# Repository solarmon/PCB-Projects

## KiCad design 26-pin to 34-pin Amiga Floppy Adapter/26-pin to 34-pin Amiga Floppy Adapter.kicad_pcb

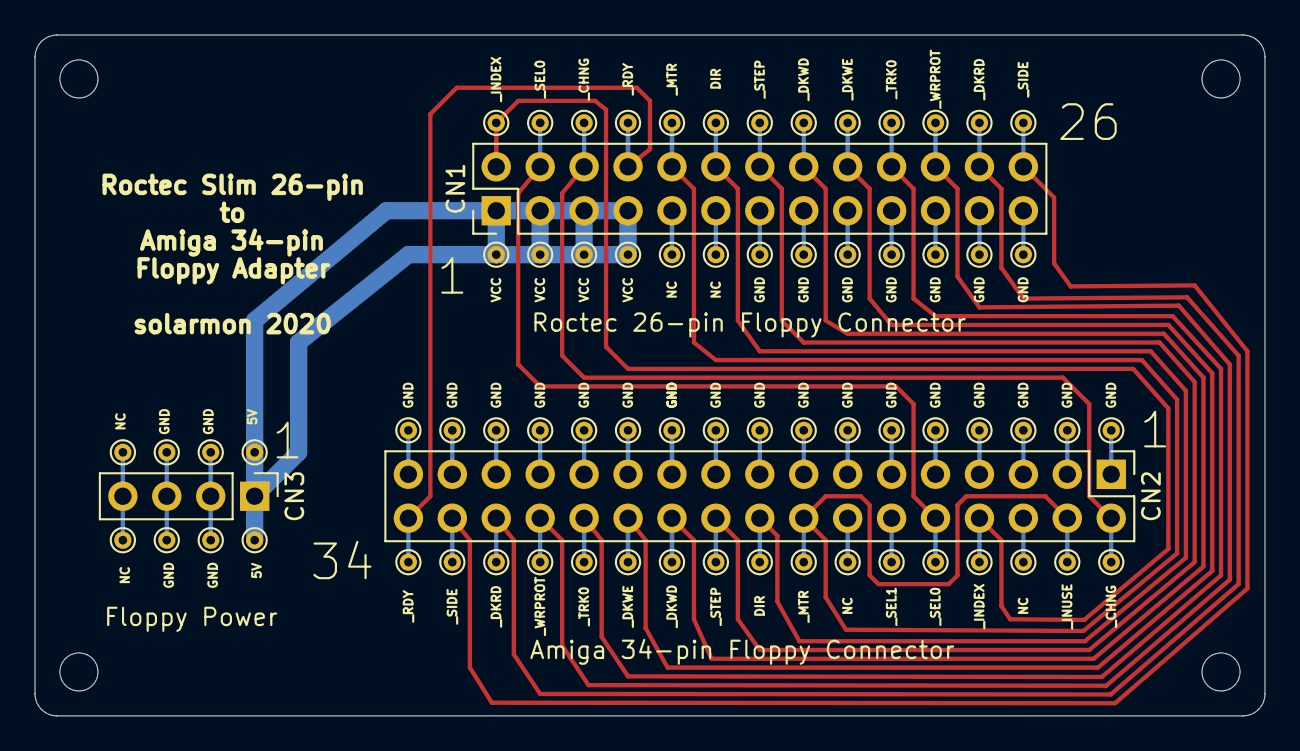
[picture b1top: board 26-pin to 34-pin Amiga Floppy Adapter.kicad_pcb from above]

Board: 2 copper layers, 71.1 x 39.4 mm, 3 parts (0 on the bottom side), 15 nets.

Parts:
CN1: Conn_02x13_Odd_Even; PinHeader_2x13_P2.54mm_Vertical
CN2: Conn_02x17_Odd_Even; PinHeader_2x17_P2.54mm_Vertical
CN3: Conn_01x04; PinHeader_1x04_P2.54mm_Vertical

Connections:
/DIR: CN1.12, CN2.18
/_CHNG: CN1.6, CN2.2
/_DKRD: CN1.24, CN2.30
/_DKWD: CN1.16, CN2.22
/_DKWE: CN1.18, CN2.24
/_INDEX: CN1.2, CN2.8
/_INUSE: CN1.10, CN2.4, CN2.16
/_RDY: CN1.8, CN2.34
/_SEL0: CN1.4, CN2.10
/_SIDE: CN1.26, CN2.32
/_STEP: CN1.14, CN2.20
/_TRK0: CN1.20, CN2.26
/_WRPROT: CN1.22, CN2.28
GND: CN1.13, CN1.15, CN1.17, CN1.19, CN1.21, CN1.23, CN1.25, CN2.1, CN2.3, CN2.5, CN2.7, CN2.9, CN2.11, CN2.13, CN2.15, CN2.17, CN2.19, CN2.21, CN2.23, CN2.25, CN2.27, CN2.29, CN2.31, CN2.33, CN3.2, CN3.3
VCC: CN1.1, CN1.3, CN1.5, CN1.7, CN3.1

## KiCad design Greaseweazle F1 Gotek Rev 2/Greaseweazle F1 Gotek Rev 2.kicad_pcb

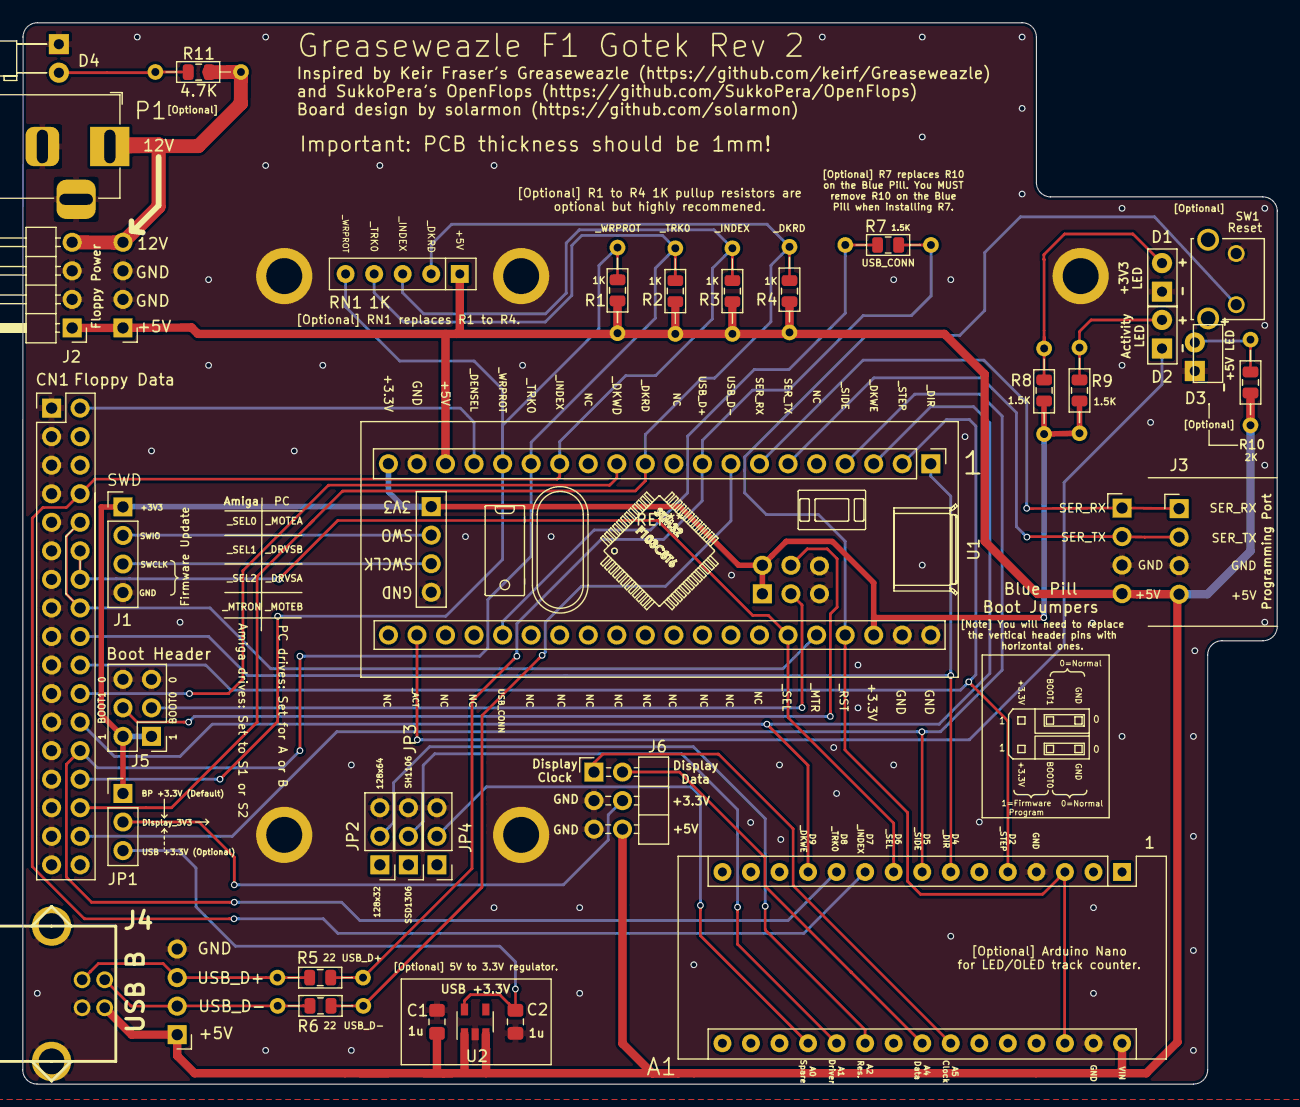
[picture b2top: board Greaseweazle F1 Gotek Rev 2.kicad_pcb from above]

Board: 2 copper layers, 111.6 x 94.4 mm, 53 parts (0 on the bottom side), 40 nets.

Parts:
A1: Arduino_Nano_v3.x; Arduino_Nano
C1, C2: 1u; C_0805_2012Metric_Pad1.15x1.40mm_HandSolder
CN1: Floppy Data; PinHeader_2x17_P2.54mm_Vertical
D1: +3V3 LED; LED_D3.0mm_Horizontal_O6.35mm_Z10.0mm
D2: ACT LED; LED_D3.0mm_Horizontal_O6.35mm_Z10.0mm
D3, D4: +5V LED; LED_D3.0mm_Horizontal_O3.81mm_Z6.0mm
H1, H2, H3, H4, H5: MountingHole_Pad; MountingHole_M3_Pad
J1: SWD; PinHeader_1x04_P2.54mm_Vertical
J1#2, J2, J3: PinHeader_1x04_P2.54mm_Vertical; PinHeader_1x04_P2.54mm_Horizontal
J2#2: Floppy Power; PinHeader_1x04_P2.54mm_Horizontal
J3#2: Programming Port; PinHeader_1x04_P2.54mm_Horizontal
J4: USB B; conn_usb_B
J5: Boot Header; PinHeader_2x03_P2.54mm_Vertical
J6: LEDC68; PinHeader_2x03_P2.54mm_Horizontal
JP1: +3.3V Jumper; PinHeader_1x03_P2.54mm_Vertical
JP2: OLED Resolution; PinHeader_1x03_P2.54mm_Vertical
JP3: OLED Driver; PinHeader_1x03_P2.54mm_Vertical
JP4: SPARE; PinHeader_1x03_P2.54mm_Vertical
P1: 12V Power; BarrelJack_Horizontal
R1, R2, R3, R4, R5, R6, R7, R8, R9, R10, R11: R_Axial_DIN0204_L3.6mm_D1.6mm_P7.62mm_Horizontal
R1#2, R2#2, R3#2, R4#2: 1K; R_0805_2012Metric
R5#2, R6#2: 22; R_0805_2012Metric
R7#2, R8#2, R9#2: 1.5K; R_0805_2012Metric
R10#2: 2K; R_0805_2012Metric
R11#2: 4.7K; R_0805_2012Metric
RN1: 1K; R_Array_SIP5
SW1: Reset; PUSH_BUTTON_RIGHT_ANGLE
U1: Blue Pill; YAAJ_BluePill_SWD_1_BootPins
U2: AP2112K-3.3; SOT-23-5

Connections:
+3V3: J1.1, J5.1, J5.2, JP1.1, R8.2, R8#2.2, R9.2, R9#2.2, U1.20, U1.38, U1.41, U1.45, U1.48
+5V: A1.30, C1.1, J1#2.1, J2.1, J2#2.1, J3.4, J3#2.4, J4.1, J6.6, R1.1, R1#2.1, R2.1, R2#2.1, R3.1, R3#2.1, R4.1, R4#2.1, R10.2, R10#2.2, RN1.1, U1.18, U2.1, U2.3
+12V: J2.4, J2#2.4, P1.1, R11.1, R11#2.2
/BOOT0: J5.3, U1.46
/BOOT1: J5.4, U1.49
/Display_3V3: J6.4, JP1.2
/Display_Clock: A1.24, J6.1
/Display_Data: A1.23, J6.2
/JP_OLED_DR: A1.20, JP3.2
/JP_OLED_RES: A1.21, JP2.2
/JP_SPARE: A1.19, JP4.2
/SER_RX: J3.1, J3#2.1, U1.7
/SER_TX: J3.2, J3#2.2, U1.6
/SWD_SWCLK: J1.3, U1.43
/SWD_SWIO: J1.2, U1.42
/USB_3V3: C2.1, JP1.3, U2.5
/USB_CONN: R7.2, R7#2.2, U1.25
/USB_D+: R5.2, R5#2.2, R7.1, R7#2.1, U1.9
/USB_D-: R6.2, R6#2.2, U1.8
/_ACT: D2.1, U1.22
/_DENSEL: CN1.2, U1.17
/_DIR: A1.7, CN1.18, U1.1
/_DKRD: CN1.30, R4.2, R4#2.2, RN1.2, U1.11
/_DKWD: CN1.22, U1.12
/_DKWE: A1.12, CN1.24, U1.3
/_INDEX: A1.10, CN1.8, R3.2, R3#2.2, RN1.3, U1.14
/_MTR: CN1.10, CN1.16, U1.36
/_RST: A1.3, A1.28, SW1.1, U1.37
/_SEL: A1.9, CN1.12, CN1.14, U1.35
/_SIDE: A1.8, CN1.32, U1.4
/_STEP: A1.5, CN1.20, U1.2
/_TRK0: A1.11, CN1.26, R2.2, R2#2.2, RN1.4, U1.15
/_WRPROT: CN1.28, R1.2, R1#2.2, RN1.5, U1.16
GND: A1.4, A1.29, C1.2, C2.2, CN1.1, CN1.3, CN1.5, CN1.7, CN1.9, CN1.11, CN1.13, CN1.15, CN1.17, CN1.19, CN1.21, CN1.23, CN1.25, CN1.27, CN1.29, CN1.31, CN1.33, D1.1, D3.1, D4.1, H1.1, H2.1, H3.1, H4.1, H5.1, J1.4, J1#2.4, J2.2, J2.3, J2#2.2, J2#2.3, J3.3, J3#2.3, J4.4, J4.5, J5.5, J5.6, J6.3, J6.5, JP2.3, JP3.3, JP4.3, P1.2, P1.3, SW1.2, U1.19, U1.39, U1.40, U1.44, U1.47, U1.50, U2.2
unnamed: D1.2, R8.1, R8#2.1
unnamed: D2.2, R9.1, R9#2.1
unnamed: D3.2, R10.1, R10#2.1
unnamed: D4.2, R11.2, R11#2.1
unnamed: J1#2.2, J4.2, R6.1, R6#2.1
unnamed: J1#2.3, J4.3, R5.1, R5#2.1

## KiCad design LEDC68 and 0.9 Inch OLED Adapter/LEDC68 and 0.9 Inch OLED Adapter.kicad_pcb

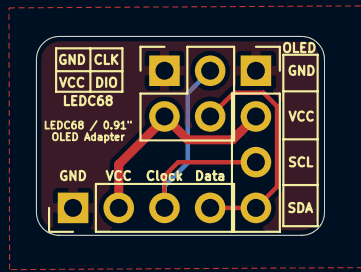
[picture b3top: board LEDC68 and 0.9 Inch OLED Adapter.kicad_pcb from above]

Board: 2 copper layers, 16.0 x 11.0 mm, 3 parts (0 on the bottom side), 4 nets.

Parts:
J1: Conn_01x04; PinSocket_1x04_P2.54mm_Vertical
J2: Conn_02x04_Odd_Even; PinSocket_2x02_P2.54mm_Vertical
J3: Conn_01x04_Male; PinHeader_1x04_P2.54mm_Vertical

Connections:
/CLK: J1.3, J2.3, J3.3
/DIO: J1.4, J2.4, J3.4
GND: J1.1, J2.1, J3.1
VCC: J1.2, J2.2, J3.2
